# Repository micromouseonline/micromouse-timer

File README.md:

# micromouse-timer
Hardware and software for a micromouse classic contest timing system

## Design goals
Many micromouse timing systems rely on devices placed in the posts to create a break-beam arrangement. An emitter in one post produces an optical signal that is detected by a matched receiver in the other post. Commercial break-beam devices are available from companies like Omron but they are very expensive, Simpler arrangements an be made with just an LED and phototransistor. For the most reliable operation, the measuring setup really needs to control both the emitter and detector synchronously so that it can detect the breaking of the beam under a wide range of ambient lighting conditions.

This need to connect one controller to both posts makes it necesary to get access to the posts from under the maze. Not only will that require the maze to be raised off the floor by some amount, it makes it very difficult to move the gates after the maze has been set up. Ideally, any timing system should not need any physical connections between components in the maze.

The APEC maze uses a gate sensor system that can be placed anywhere and only needs to be present on one side of the opening. It manages this by using a reflective sensor that measures the distance to the far post. These sensors are similar to those used in the popular Sharp distance sensors by they are have a much faster response time. The Sharp sensors canot be polled every milisecond to get high resolution timing. Unfortunately, making the reflective sensors is quite complicated and requires a certain amount of signal processing circuitry. It is not something that is terribly easy to reproduce.

When making a timing gate sensor, consideration must be given to the robots in the maze. They typically generate very high intensity pulses of IR or visible red light from multiple emitters at 1000Hz or more. Not only should the timing system be unaffected by these pulses, it should also not interfere with the robot's ablity to make measurements. Thus, the robot must not cause timing errors and the timing syste must not make the robots crash.

Finally, there is the issue of ambient lighting levels. These are variable from venue to venue and may vary greatly even during a contest. A venue with natural light may have direct sunlight into the room and, clearly, that light will move around during the day. Other sources of interfering ambient light might include camera lights and camera flashguns. theese too should not interfere with the operation of the timing system.

With so many constraints, it would be natural to seek ever more sophisticated solutions to overcome them.

After several experiments with 'clever' designs, this project tries to make everything as simple as possible.

## Components
There are four components for this timing system
1. gate emitters  - these are just blue LEDs connected to a single Lithium cell with a single current limit resistor. They operate continuously for up to 36 hours between charges.
2. gate receivers - these have a phototransistor with a single load resistor connected to an analogue input channel on an Arduino. The Arduino is also connected to a small 433MHz radio module so that it can send detected changes to a timing controller. Again, a single Lithium cell provides power for at least 20 hours operation.
3. gate controller - the controller is connected directly to the timing management computer with a USB-serial link. It also has a radio receiver so that it can obtain event information from the gate receivers. Each gate receiver sends encoded packets to identify the event and the gate ID. The controller performs the actual timing function and all the data can be stored on an SD card for independent operation or to provide a backup. Power can come from the host USB connection, batteries or a separate power supply. Optionally, a Bluetooth conenction could be made to the host. Sinca all the communication with the gates is wireless, the controller can be placed several metres away from the maze and there are no trailing wires to the maze.
4. timing manager - the software running on the host computer that accepts timing information from the controller, presents it on the display screens and maintains the contest results.

## Gate Operation
Each gate has an emitter and a receiver.

### Emitters
The emitter generates a continuous beam of illumination using blue light. Green light would be a good alternative. While apparently very bright to the human eye, typical micromouse sensor will be relatively insensitive to these wavelengths and, in any case, will perceive the illumnation as part of the background and so it should be compensated for. Blue LEDs have quite high forward voltages of around 2.8 to 3.0 Volts but can still be run from a single Lithium cells with a small series current limiting resistor. Using a resistor value of 39 Ohms with the chosen device limits the maximum current to around 27mA with a fully charged battery at 4.2Volts. As the battery discharges to a nominal 3.7 Volts, the current decreases to about 15mA.

The battery is a Nokia BL-4S with a nominal capacity of 860 mAhr. Once turned on, there should be sufficient capacity for at least 36 hours operation.

A TP4056-based battery charge and protect circuit prevents over discharge of the battery and allows for easy re-charging from a 5V source such as a cell-phone charger of portable power bank.

The emmitter assembly is entirely contained within a typical plastic classic wall. Light shines through a hole in the end of the wall and a corresponding hole is a post. Where the gate must be perpendicular to the wall, a special post is used that contains an embedded reflector at 45 degrees. The reflecto involves a failry large aamount of light loss but is still sufficent for the task. Straight-through emitters might benefit from lower intensity and this could be provided with an additional switch to change the current limit resistor.

### Detectors
The detector circuit is minimal. It consistes of a TEPT5600 visible light phototransistor with a 2200Ohm load resistor on the emitter. The transistor emitter is connected directly to an analogue channel on an arduino mini-pro. The load resistor is selected to give a reading of between 20 and 60 counts when illuminated only by the LED in the timing gate in its normal operating configuration. This is quite a low sensitivity but it ensures that operation will be relatively unaffected even by quite bright ambient illumination right up to the point of saturation of the phototransistor

Attached to a software serial TX pin on the Arduino is a self-contained radio transeiver used only in its transmit mode. the radio is powered down until the gate is interrupted. When messages are to be sent, the radio is powered up, placed in transmit mode and the message is transmitted several times to ensure reliable communication. Aferards, the radio is powered down again to reduce current consumption and prevent interference.

All the radios in the system operate on the same frequency but there should be no natural circumstance where more than one transmits at a time. Thus, the controller needs only one radio and can distinguish the message source from its content.

Like the emitter, the circuitry all fits inside a typical classic maze wall and runs from a BL-4S battery using the same type of TP4056 charge/protect module. In normal operation, the Arduino draws only 12mA and the brief periods of transmission double that for a second or two. Continuous operation should be possible for at least 50 hours with a fully charged BL-4S battery.

### Controller
At the heart of the timing operation is the controller. An Arduino is connected to another LINX radio module which is running continuously in receive mode. It listens for packets from the gate detectors and runs a state machine that looks after all the timing functions related to the current contest.

While intended primarily for micromouse, the same controller could be used for drag race, line follower and time trial contests. Some additional care would be needed to distinguish the transmissions from gates in other contests. The controller passes timing and event notfications to the host computer running event management software using a USB-serial bridge. The same connection can provide power.

So that the controller can be used stand-alone and/or act as a backup to automatic timing, it also has an LCD display and a number of manual buttons that set the state of the system and provide manual gate inputs if needed.

Internally, an SD card records all the incoming and outgoing messages so that they can be retreived for later analysis and toserve as an auxiliary store in case of an error or failure in the management software. Files are time stamped using a data from a battery-backed real time clock module. Note that the RTC battery is not rechargeable and annual maintenance should be carried out to replace the battery and ensure thatthe time and date are correct.

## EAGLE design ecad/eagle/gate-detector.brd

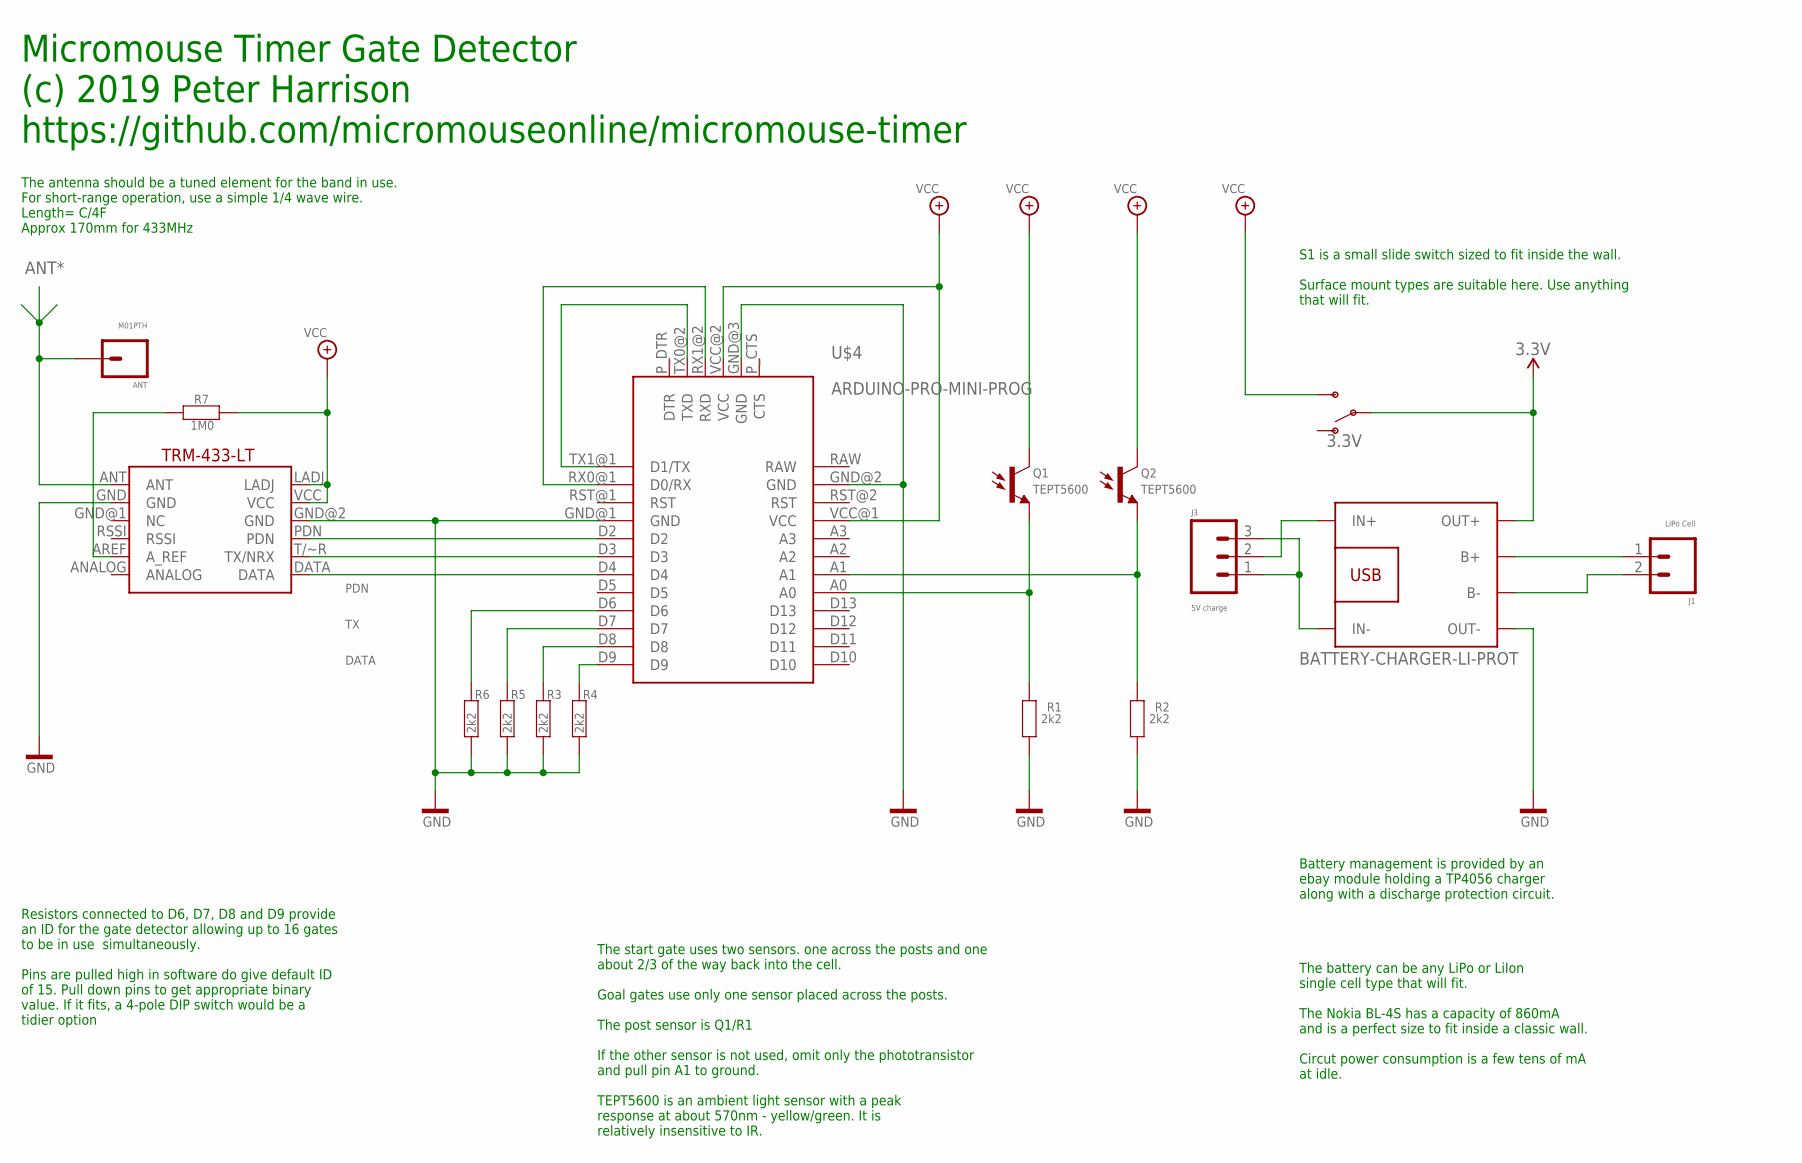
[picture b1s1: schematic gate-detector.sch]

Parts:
3.3V: SWITCH-SPDT-PTH-11.6X4.0MM-KIT; SWITCH_SPDT_PTH_11.6X4.0MM_KIT
ANT: M01PTH; 1X01
J1: LiPo Cell; 1X02_RA_PTH_MALE_MILL
J3: 5V charge; 1X03_RA_PTH_MILL
Q1, Q2: TEPT5600; PHOTOTRANSISTOR-TO5-SIDE
R1, R2, R3, R4, R5, R6: 2k2; AXIAL-0207_0.4
R7: 1M0; AXIAL-0207_0.4
U$1: TRM-433-LT; LINX-TRM-433-LT
U$2: BATTERY-CHARGER-LI-PROT
U$4: ARDUINO-PRO-MINI-PROG

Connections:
3.3V: 3.3V.2, U$2.OUT+
ANT*: ANT.1, U$1.ANT
DATA: U$1.DATA, U$4.D4
GND: R1.1, R2.1, R3.1, R4.1, R5.1, R6.1, U$1.GND, U$1.GND@2 (GND), U$2.OUT-, U$4.GND@1 (GND), U$4.GND@2 (GND), U$4.GND@3 (GND)
unnamed: Q2.E, R2.2, U$4.A1
unnamed: J1.1, U$2.B+
unnamed: R4.2, U$4.D9
unnamed: R3.2, U$4.D8
unnamed: R5.2, U$4.D7
unnamed: Q1.E, R1.2, U$4.A0
unnamed: J1.2, U$2.B-
unnamed: R6.2, U$4.D6
unnamed: R7.2, U$1.AREF (A_REF)
unnamed: J3.2, U$2.IN+
unnamed: J3.1, J3.3, U$2.IN-
unnamed: U$4.TX0@2 (TXD), U$4.TX1@1 (D1/TX)
unnamed: U$4.RX0@1 (D0/RX), U$4.RX1@2 (RXD)
PDN: U$1.PDN, U$4.D2
RAW: U$4.RAW
TX: U$1.T/~R (TX/NRX), U$4.D3
VCC: 3.3V.3 (S), Q1.C, Q2.C, R7.1, U$1.LADJ, U$1.VCC, U$4.VCC@1 (VCC), U$4.VCC@2 (VCC)

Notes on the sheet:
The antenna should be a tuned element for the band in use. For short-range operation, use a simple 1/4 wave wire. Length= C/4F Approx 170mm for 433MHz
The start gate uses two sensors. one across the posts and one about 2/3 of the way back into the cell. Goal gates use only one sensor placed across the posts. The post sensor is Q1/R1 If the other sensor is not used, omit only the phototransistor and pull pin A1 to ground. TEPT5600 is an ambient li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
The battery can be any LiPo or LiIon single cell type that will fit. The Nokia BL-4S has a capacity of 860mA and is a perfect size to fit inside a classic wall. Circut power consumption is a few tens of mA at idle.
Battery management is provided by an ebay module holding a TP4056 charger along with a discharge protection circuit.
Micromouse Timer Gate Detector (c) 2019 Peter Harrison https://github.com/micromouseonline/micromouse-timer
S1 is a small slide switch sized to fit inside the wall. Surface mount types are suitable here. Use anything that will fit.
Resistors connected to D6, D7, D8 and D9 provide an ID for the gate detector allowing up to 16 gates to be in use simultaneously. Pins are pulled high in software do give default ID of 15. Pull down pins to get appropriate binary value. If it fits, a 4-pole DIP switch would be a tidier option

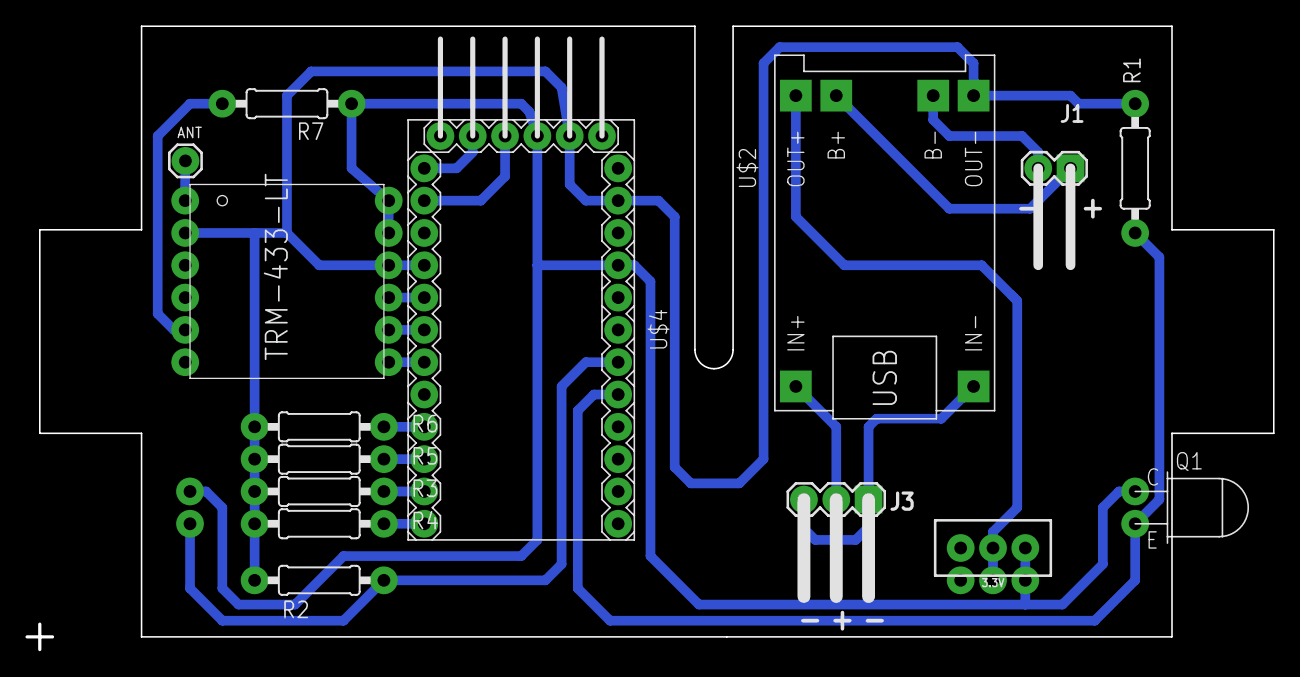
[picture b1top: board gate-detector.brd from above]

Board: 2 copper layers, 97.9 x 48.9 mm, 16 parts (1 on the bottom side), 20 nets.

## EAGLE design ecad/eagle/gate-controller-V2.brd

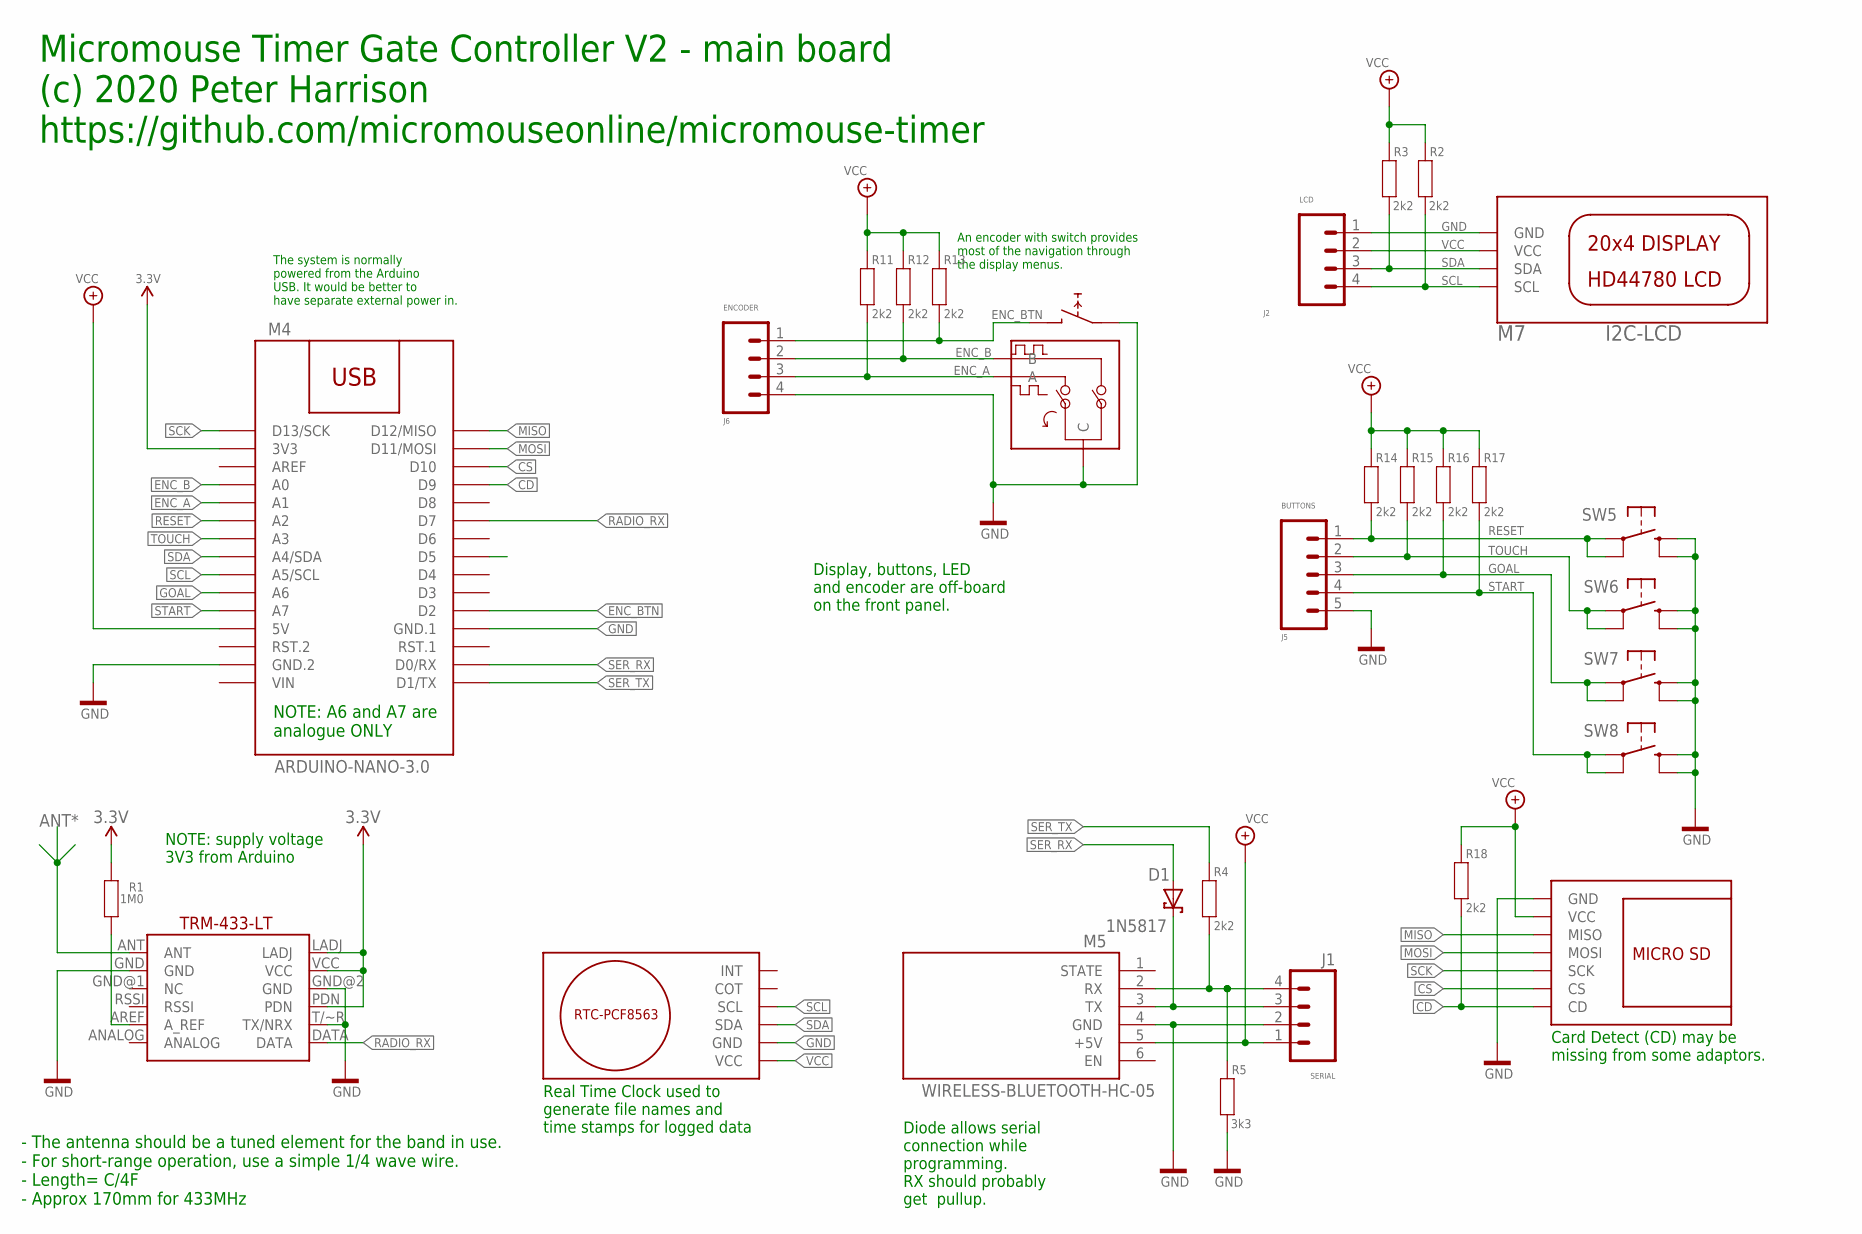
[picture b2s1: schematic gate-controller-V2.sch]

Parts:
D1: 1N5817; DO35-7
J1: SERIAL; 1X04
J2: LCD; 1X04
J5: BUTTONS; 1X05
J6: ENCODER; 1X04
M2: RTC-PCF8563
M3: TRM-433-LT; LINX-TRM-433-LT
M4: ARDUINO-NANO-3.0
M5: WIRELESS-BLUETOOTH-HC-05
M6: MICRO-SD-ADAPTOR
R1: 1M0; AXIAL-0207_0.4
R2, R3, R4, R11, R12, R13, R14, R15, R16, R17, R18: 2k2; AXIAL-0207_0.4
R5: 3k3; AXIAL-0207_0.4

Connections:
3V3: M3.LADJ, M3.PDN, M3.VCC, M4.3V3, R1.2
ANT*: M3.ANT
CD: M4.D9, M6.CD, R18.1
CS: M4.D10, M6.CS
D5: M4.D5
ENC_A: J6.3, M4.A1, R11.1
ENC_B: J6.2, M4.A0, R12.1
ENC_BTN: J6.1, M4.D2, R13.1
GND: J1.2, J2.1, J5.5, J6.4, M2.GND, M3.GND, M3.GND@2 (GND), M3.T/~R (TX/NRX), M4.GND@1 (GND.2), M4.GND@2 (GND.1), M5.4 (GND), M6.GND, R5.1
GOAL: J5.3, M4.A6, R16.1
MISO: M4.D12 (D12/MISO), M6.MISO
MOSI: M4.D11 (D11/MOSI), M6.MOSI
unnamed: M3.AREF (A_REF), R1.1
unnamed: J1.4, M5.2 (RX), R4.1, R5.2
unnamed: D1.C, J1.3, M5.3 (TX)
RADIO_RX: M3.DATA, M4.D7
RESET: J5.1, M4.A2, R14.1
SCK: M4.D13 (D13/SCK), M6.SCK
SCL: J2.4, M2.SCL, M4.A5 (A5/SCL), R2.1
SDA: J2.3, M2.SDA, M4.A4 (A4/SDA), R3.1
SER_RX: D1.A, M4.RX0 (D0/RX)
SER_TX: M4.TX1 (D1/TX), R4.2
START: J5.4, M4.A7, R17.1
TOUCH: J5.2, M4.A3, R15.1
VCC: J1.1, J2.2, M2.VCC, M4.5V, M5.5 (+5V), M6.VCC, R2.2, R3.2, R11.2, R12.2, R13.2, R14.2, R15.2, R16.2, R17.2, R18.2
VIN: M4.VIN

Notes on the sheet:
- The antenna should be a tuned element for the band in use. - For short-range operation, use a simple 1/4 wave wire. - Length= C/4F - Approx 170mm for 433MHz
Micromouse Timer Gate Controller V2 - main board (c) 2020 Peter Harrison https://github.com/micromouseonline/micromouse-timer
Card Detect (CD) may be missing from some adaptors.
Diode allows serial connection while programming. RX should probably get pullup.
An encoder with switch provides most of the navigation through the display menus.
NOTE: supply voltage 3V3 from Arduino
Real Time Clock used to generate file names and time stamps for logged data
Display, buttons, LED and encoder are off-board on the front panel.
NOTE: A6 and A7 are analogue ONLY
The system is normally powered from the Arduino USB. It would be better to have separate external power in.

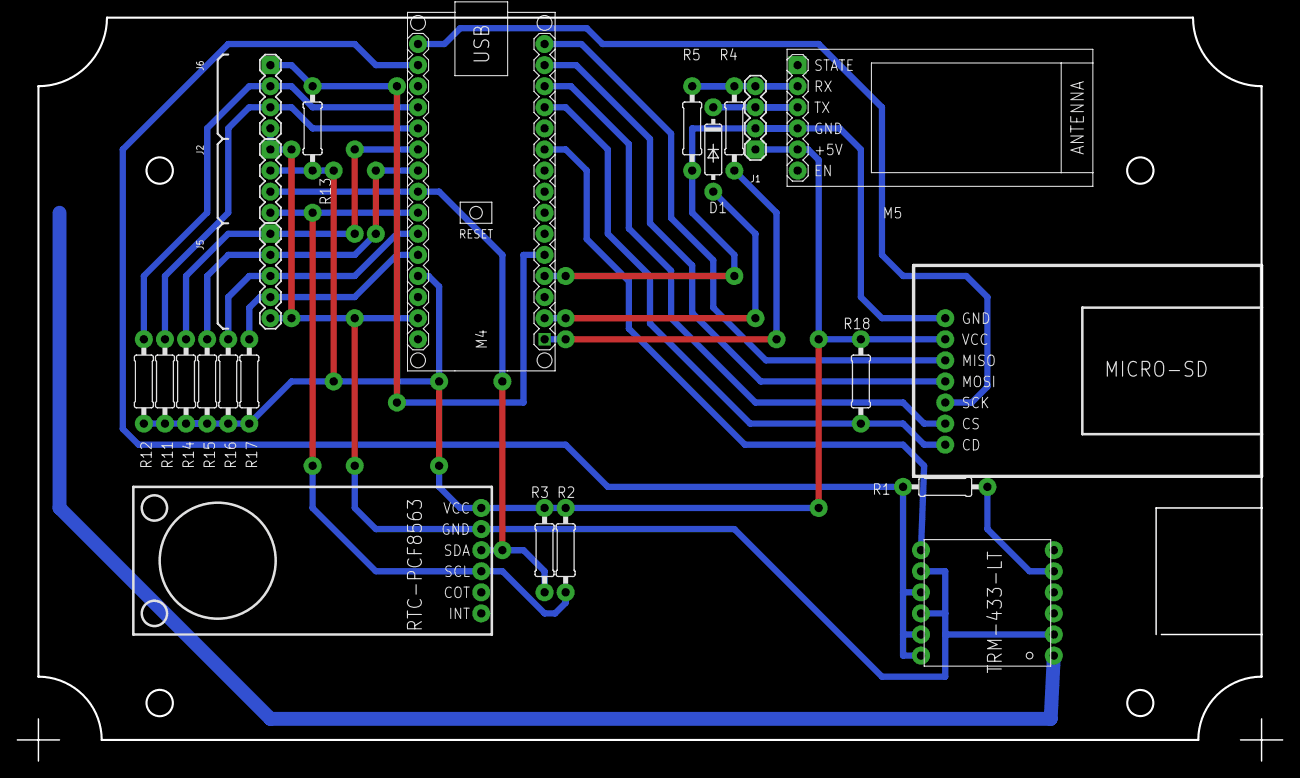
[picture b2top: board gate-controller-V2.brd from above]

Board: 2 copper layers, 152.3 x 89.5 mm, 24 parts (0 on the bottom side), 23 nets.

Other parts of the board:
U$1: HAMMOND-1595-C-BOARD

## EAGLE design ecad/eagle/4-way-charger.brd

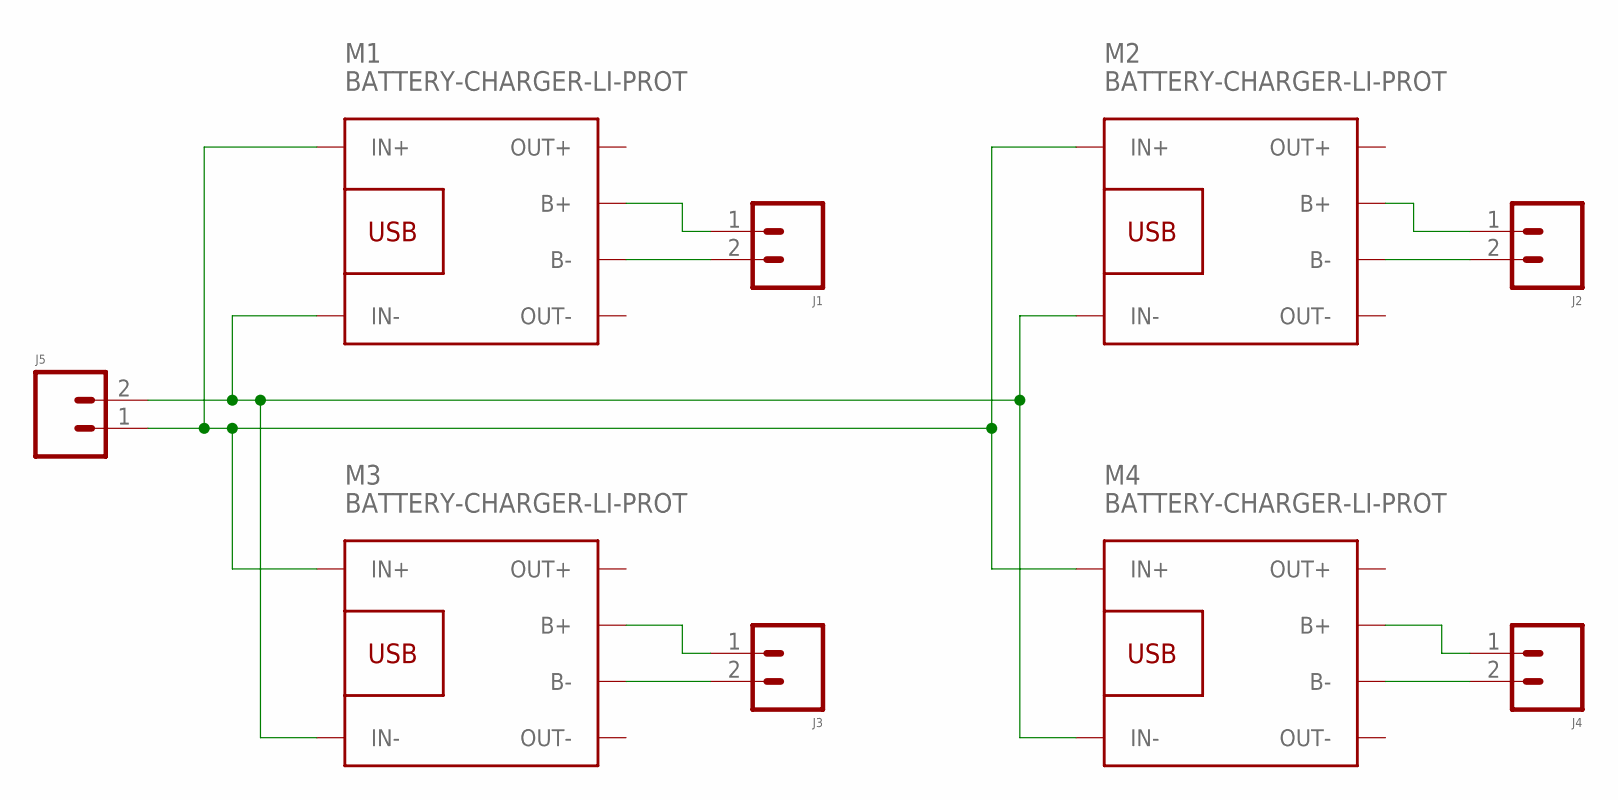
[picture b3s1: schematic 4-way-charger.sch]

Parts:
J1, J2, J3, J4, J5: M02RA_MALE_MILL; 1X02_RA_PTH_MALE_MILL
M1, M2, M3, M4: BATTERY-CHARGER-LI-PROT

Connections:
unnamed: J3.2, M3.B-
unnamed: J3.1, M3.B+
unnamed: J1.2, M1.B-
unnamed: J1.1, M1.B+
unnamed: J2.2, M2.B-
unnamed: J2.1, M2.B+
unnamed: J4.2, M4.B-
unnamed: J4.1, M4.B+
unnamed: J5.2, M1.IN-, M2.IN-, M3.IN-, M4.IN-
unnamed: J5.1, M1.IN+, M2.IN+, M3.IN+, M4.IN+

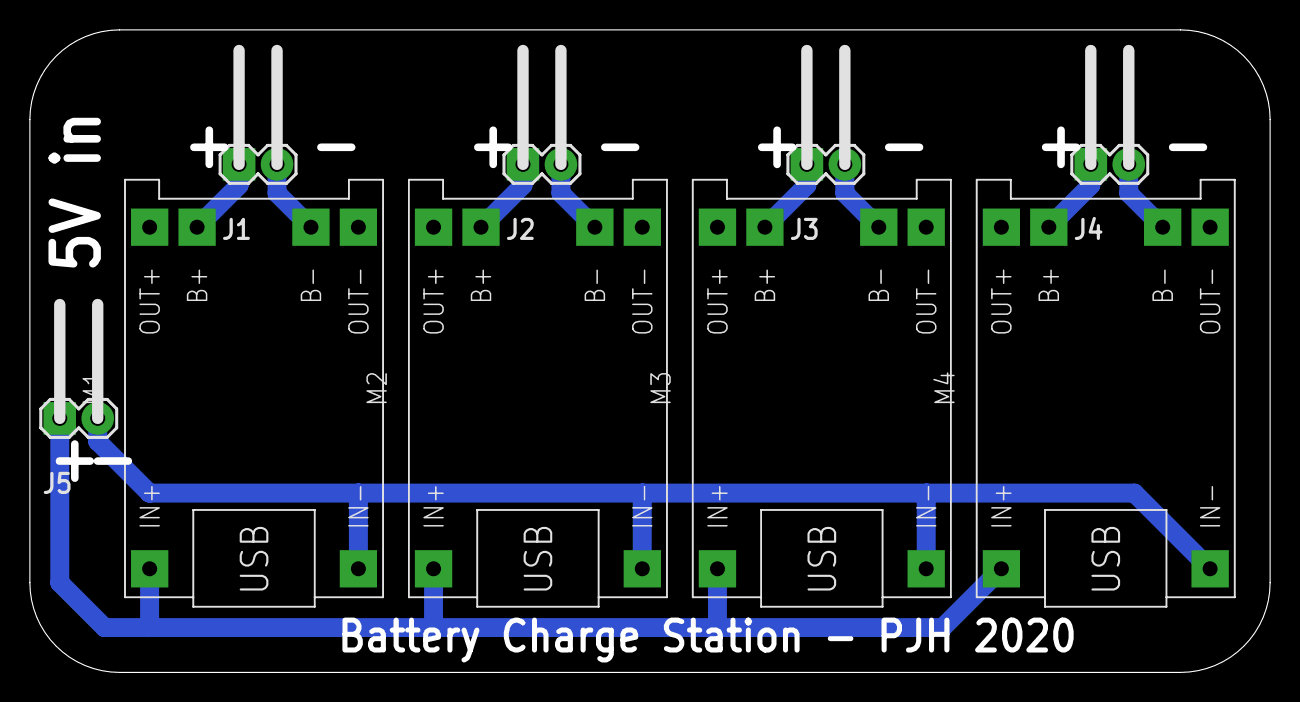
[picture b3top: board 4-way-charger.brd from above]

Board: 2 copper layers, 83.0 x 43.0 mm, 9 parts (0 on the bottom side), 10 nets.

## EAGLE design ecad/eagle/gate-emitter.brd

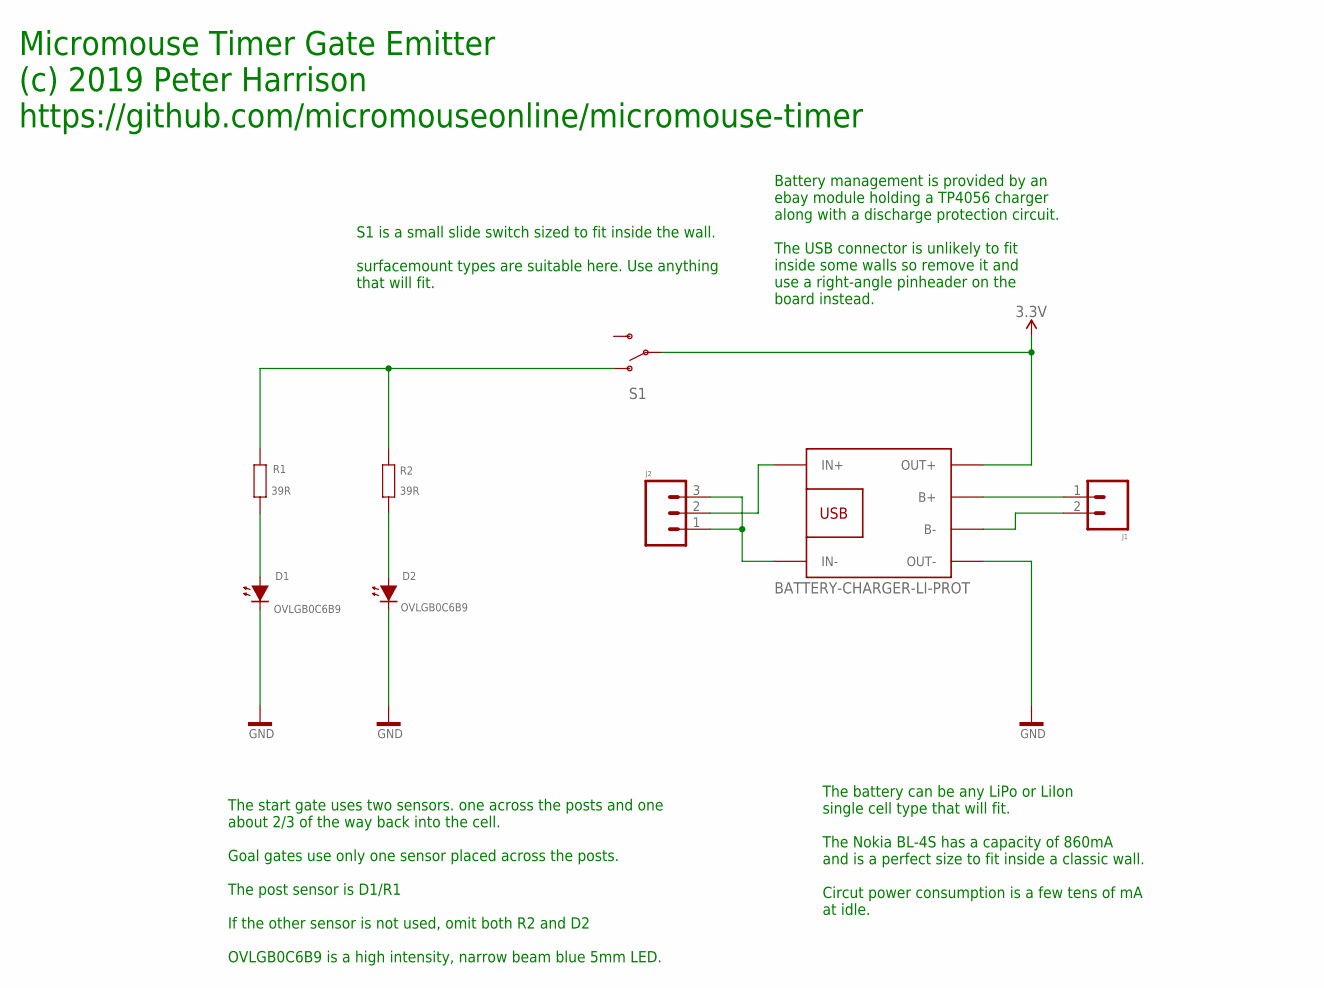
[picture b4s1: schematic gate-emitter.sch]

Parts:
D1, D2: OVLGB0C6B9; LED5MM-H
J1: M02RA_MALE_MILL; 1X02_RA_PTH_MALE_MILL
J2: M03RA_MALE; 1X03_RA_PTH_MILL
R1, R2: 39R; AXIAL-0207_0.4
S1: SWITCH-SPDT-PTH-11.6X4.0MM; SWITCH_SPDT_PTH_11.6X4.0MM
U$2: BATTERY-CHARGER-LI-PROT

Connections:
3.3V: S1.2, U$2.OUT+
GND: D1.C, D2.C, U$2.OUT-
unnamed: R1.2, R2.2, S1.1 (O)
unnamed: J1.1, U$2.B+
unnamed: D1.A, R1.1
unnamed: D2.A, R2.1
unnamed: J2.2, U$2.IN+
unnamed: J2.1, J2.3, U$2.IN-
unnamed: J1.2, U$2.B-

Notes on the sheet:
The start gate uses two sensors. one across the posts and one about 2/3 of the way back into the cell. Goal gates use only one sensor placed across the posts. The post sensor is D1/R1 If the other sensor is not used, omit both R2 and D2 OVLGB0C6B9 is a high intensity, narrow beam blue 5mm LED.
The battery can be any LiPo or LiIon single cell type that will fit. The Nokia BL-4S has a capacity of 860mA and is a perfect size to fit inside a classic wall. Circut power consumption is a few tens of mA at idle.
Battery management is provided by an ebay module holding a TP4056 charger along with a discharge protection circuit. The USB connector is unlikely to fit inside some walls so remove it and use a right-angle pinheader on the board instead.
Micromouse Timer Gate Emitter (c) 2019 Peter Harrison https://github.com/micromouseonline/micromouse-timer
S1 is a small slide switch sized to fit inside the wall. surfacemount types are suitable here. Use anything that will fit.

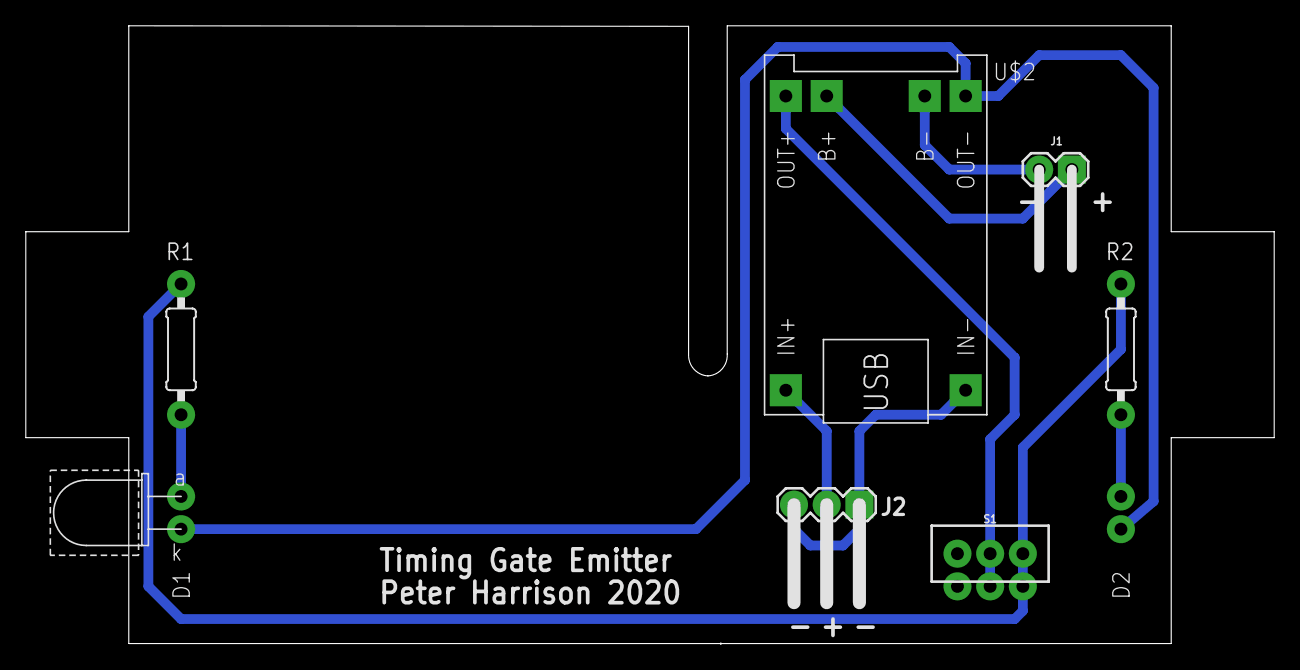
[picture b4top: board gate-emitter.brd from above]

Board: 2 copper layers, 97.0 x 48.0 mm, 8 parts (1 on the bottom side), 9 nets.

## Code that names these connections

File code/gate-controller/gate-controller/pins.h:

#ifndef PINS_H
#define PINS_H

#include <Arduino.h>

/// Pin Assignments
const int LED_2 = 3;
const int LED_3 = 4;
const int LED_4 = 5;
const int LED_5 = 6;

const int RADIO_RX = 7;
const int RADIO_TX = 8;
const int SD_DETECT = 9;
const int SD_SELECT = 10;
const int SD_MOSI = 11;
const int SD_MISO = 12;
const int SD_SCK = 13;

const int ENC_BTN = 2;
const int ENC_A = A0;
const int ENC_B = A1;

const int BUTTON_ARM = A7;
const int BUTTON_START = A6;  // analogue only
const int BUTTON_GOAL = A3;   // analogue only
const int BUTTON_RESET = A2;

const int I2C_SDA = A4;
const int I2C_SCL = A5;


#endif

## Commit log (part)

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2019-12-28 add emitter schematic
2019-12-29 update detector schematic
2020-01-02 add gate controller schematic
2020-01-05 update gate controller schematics
2020-01-06 add LED display
2020-01-07 remove LED display
2020-01-07 add pullups and re-arrange buttons
2020-01-08 tidy the controller schematic a little
2020-01-13 images of the first prototype
2020-01-13 add a picture readme.md
2020-01-15 resize images of the first prototype
2020-01-16 first code commit
2020-01-16 Update the readme files
2020-01-16 Add a README to the code folder
2020-01-17 tidy up code and reduce footprint
2020-02-03 update pictures and code
2020-02-13 new pictures
2020-02-13 resize pictures
2022-06-11 update gitignore files
2022-06-11 track travis file
2022-06-11 reformat and organise gate-controller
2022-06-11 update all the images
2022-06-11 update PDF files
2022-06-11 update readme and license files
2022-06-11 update the build scripts
2022-06-11 reorganise gate detector
2022-06-11 reorganise radio RX test
2022-06-11 reorganise radio TX test
2022-06-11 reorganise SD card test
2022-06-11 update description of messages used
2022-06-11 add constants for new message set
2022-06-18 add linx radio data sheet and app note
2022-06-18 many changes to controller
2022-06-18 update the valid messages
2022-06-18 set the port used for the controller
2022-06-18 simplify the gate detector
2022-06-18 update the basic radio tests
2022-06-18 fix overflow error in keritimer
2022-06-20 remove old message definitions
2022-06-20 track the combined state of the buttons
2022-06-20 remove old state definitions
2022-06-20 add facility to reset controller from buttons
2022-06-20 update new mouse message
2022-06-20 define radio pins symbolically
2022-06-20 rework startup sequence
2022-06-20 update for time trials
2022-06-20 don't track encoder button state
2022-06-20 refactor contest type selection
2022-06-20 move some code around
2022-06-20 remove unused code
2022-06-20 move some doc files
2022-06-20 simplify the button class
2022-06-20 and a little tidy of button.h
2022-06-20 add time trial option
2022-06-22 remive unused files
2022-06-22 remove dead code
2022-06-22 rename gate message reader
2022-06-22 clear maze time when new mouse selected
2022-06-22 clean up trial_machine a little
2022-06-22 add comment about ST_GOAL state
2022-06-22 rename gate message time variable
2022-06-23 improved controller code
2022-06-23 improved detector code
2022-06-23 update version on menu
2022-07-13 tighten up the message timing
2022-07-13 improve the startup indication
2023-07-05 add all project files to repository
2023-07-13 Allow fast recovery and occlusion protection
2024-06-26 reset waits for button release
2024-06-26 only send the time once
2024-06-26 gives the radio data state names instead of numbers
2024-06-26 show state whenever it changes
2024-06-26 add comments to messages
2024-07-06 add watchdog message type
2024-07-06 send watchdog message every second
2024-07-06 reset defaults to maze timer reset with button down to change mode
2024-07-06 defines the reset vector more flexibly
2024-07-06 messages are explititly used inline
2024-07-17 create a vscode workspace
2024-07-17 go back to automatic port detection for windows
2024-07-17 add clang-format config
2024-07-17 change the message order
2024-07-17 prevent multiple messages when pressing two buttons
2024-07-18 make the gate tag available globally
2024-07-18 initialise gate tag to a known value
2024-07-18 add some commented debug messages
2024-07-18 skip run times of less than 500ms
